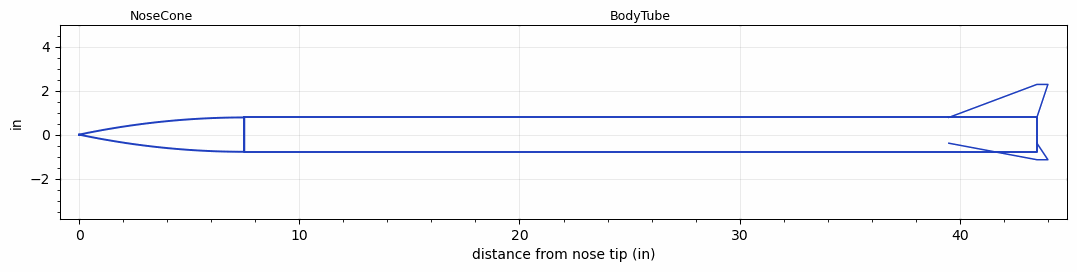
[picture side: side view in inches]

<RASAeroDocument>
 <FileVersion>2</FileVersion>
 <RocketDesign>
  <NoseCone>
   <Length>7.5</Length>
   <Diameter>1.56</Diameter>
   <Shape>Tangent Ogive</Shape>
   <Location>0</Location>
  </NoseCone>
  <BodyTube>
   <Length>36</Length>
   <Diameter>1.56</Diameter>
   <Location>7.5</Location>
   <Fin>
    <Count>3</Count>
    <Chord>4</Chord>
    <Span>1.5</Span>
    <SweepDistance>4</SweepDistance>
    <TipChord>0.5</TipChord>
    <Thickness>0.125</Thickness>
    <LERadius>0.02</LERadius>
    <Location>4</Location>
    <AirfoilSection>Hexagonal</AirfoilSection>
    <FX1>0.5</FX1>
    <FX3>0.5</FX3>
   </Fin>
  </BodyTube>
  <Surface>Camouflage Paint</Surface>
  <ModifiedBarrowman>True</ModifiedBarrowman>
  <Turbulence>True</Turbulence>
  <UseBooster1>False</UseBooster1>
  <UseBooster2>False</UseBooster2>
 </RocketDesign>
 <LaunchSite>
  <Altitude>1000</Altitude>
  <Pressure>0</Pressure>
  <RodAngle>3</RodAngle>
  <RodLength>6</RodLength>
  <Temperature>74</Temperature>
  <WindSpeed>1</WindSpeed>
 </LaunchSite>
 <Recovery>
  <Altitude1>1000</Altitude1>
  <Altitude2>1000</Altitude2>
  <DeviceType1>None</DeviceType1>
  <DeviceType2>None</DeviceType2>
  <Event1>False</Event1>
  <Event2>False</Event2>
  <Size1>1</Size1>
  <Size2>1</Size2>
  <EventType1>None</EventType1>
  <EventType2>None</EventType2>
  <CD1>1.33</CD1>
  <CD2>1.33</CD2>
 </Recovery>
 <SimulationList>
  <Simulation>
   <SustainerEngine>J530-IM  (CTI)</SustainerEngine>
   <SustainerLaunchWt>4.25</SustainerLaunchWt>
   <SustainerCG>25.61</SustainerCG>
   <SustainerIgnitionDelay>0</SustainerIgnitionDelay>
   <Booster1SeparationDelay>0</Booster1SeparationDelay>
   <Booster1IgnitionDelay>0</Booster1IgnitionDelay>
   <IncludeBooster1>False</IncludeBooster1>
   <Booster2Delay>0</Booster2Delay>
   <IncludeBooster2>False</IncludeBooster2>
   <TimetoApogee>26.1405</TimetoApogee>
   <MaxAltitude>15536.96</MaxAltitude>
   <MaxVelocity>1885.887</MaxVelocity>
  </Simulation>
  <Simulation>
   <SustainerEngine>I540WT  (CTI)</SustainerEngine>
   <SustainerLaunchWt>4.25</SustainerLaunchWt>
   <SustainerCG>24.65</SustainerCG>
   <SustainerIgnitionDelay>0</SustainerIgnitionDelay>
   <Booster1SeparationDelay>0</Booster1SeparationDelay>
   <Booster1IgnitionDelay>0</Booster1IgnitionDelay>
   <IncludeBooster1>False</IncludeBooster1>
   <Booster2Delay>0</Booster2Delay>
   <IncludeBooster2>False</IncludeBooster2>
   <TimetoApogee>22.08041</TimetoApogee>
   <MaxAltitude>9378.59</MaxAltitude>
   <MaxVelocity>1098.836</MaxVelocity>
  </Simulation>
 </SimulationList>
</RASAeroDocument>
